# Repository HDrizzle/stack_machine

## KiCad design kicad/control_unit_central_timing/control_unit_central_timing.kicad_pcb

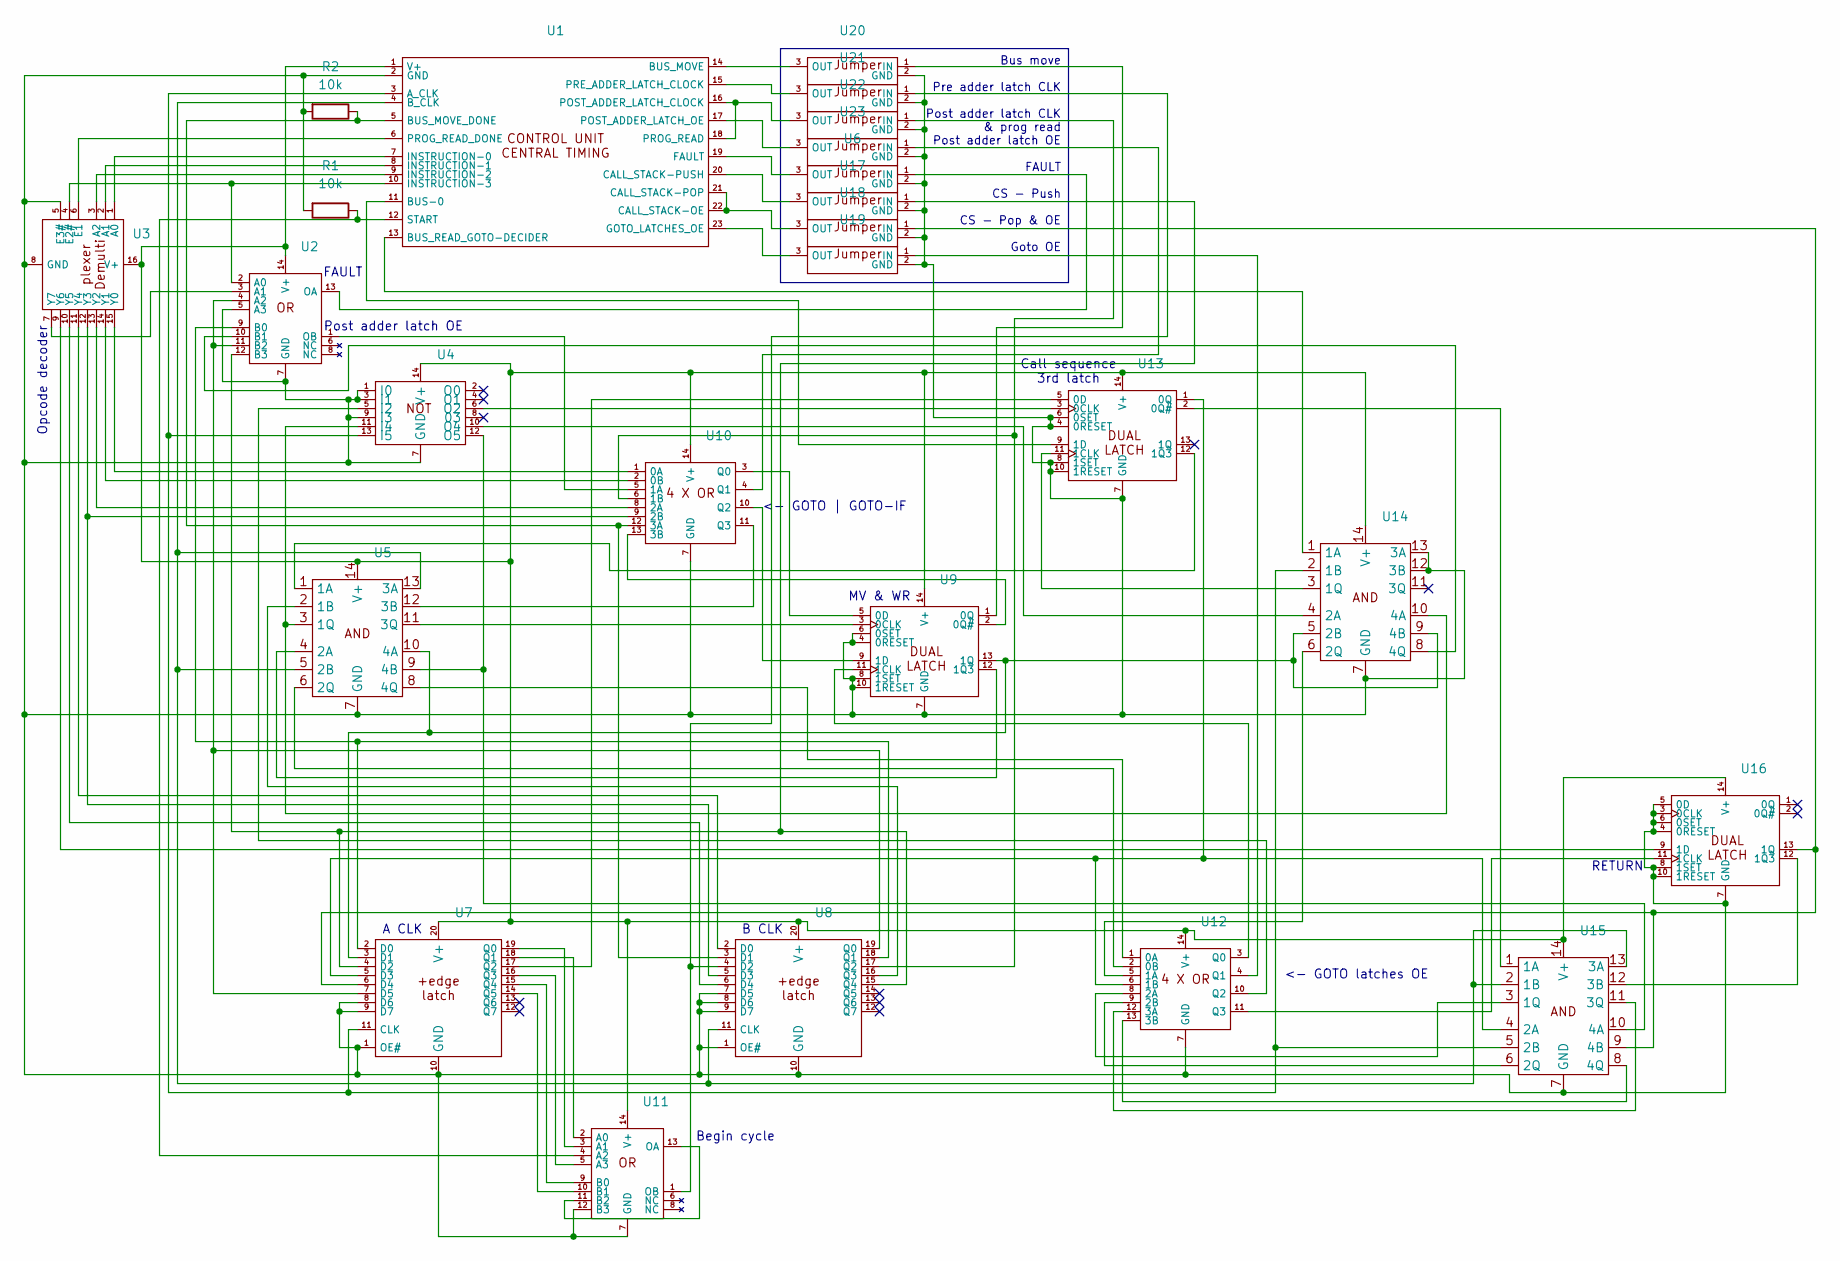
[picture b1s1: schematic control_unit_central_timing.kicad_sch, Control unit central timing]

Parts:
R1, R2: 10k; 0.4_pitch_resistor
U1: PinHeader_1x23_P2.54mm_Horizontal
U2, U4, U5, U9, U10, U11, U12, U13, U14, U15, U16: DIP-14_W7.62mm
U3: DIP-16_W7.62mm
U6, U17, U18, U19, U20, U21, U22, U23: jumper
U7, U8: DIP-20_W7.62mm

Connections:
unnamed: U1.3 (A_CLK), U4.13 (I5), U7.11 (CLK), U14.2 (1B), U15.5 (2B)
unnamed: U1.11 (BUS-0), U13.9 (1D)
unnamed: U1.14 (BUS_MOVE), U20.3 (OUT)
unnamed: R2.1, U1.5 (BUS_MOVE_DONE), U8.3 (D1), U10.12 (3A)
unnamed: U1.13 (BUS_READ_GOTO-DECIDER), U14.1 (1A)
unnamed: U1.4 (B_CLK), U5.5 (2B), U5.13 (3A), U8.11 (CLK), U15.2 (1B), U15.13 (3A)
unnamed: U1.21 (CALL_STACK-POP), U1.22 (CALL_STACK-OE), U18.3 (OUT)
unnamed: U1.20 (CALL_STACK-PUSH), U17.3 (OUT)
unnamed: U1.19 (FAULT), U6.3 (OUT)
unnamed: R1.2, R2.2, U1.2 (GND), U2.5 (A3), U2.7 (GND), U3.5 (E3#), U3.8 (GND), U4.1 (I0), U4.3 (I1), U4.7 (GND), U4.9 (I3), U5.7 (GND), U6.2 (GND), U7.1 (OE#), U7.8 (D6), U7.9 (D7), U7.10 (GND), U8.1 (OE#), U8.7 (D5), U8.8 (D6), U8.9 (D7), U8.10 (GND), U9.4 (0RESET), U9.6 (0SET), U9.7 (GND), U9.8 (1SET), U9.10 (1RESET), U10.7 (GND), U11.7 (GND), U11.12 (B3), U12.7 (GND), U13.4 (0RESET), U13.6 (0SET), U13.7 (GND), U13.8 (1SET), U13.10 (1RESET), U14.7 (GND), U14.12 (3B), U14.13 (3A), U15.7 (GND), U16.3 (0CLK), U16.4 (0RESET), U16.5 (0D), U16.6 (0SET), U16.7 (GND), U16.8 (1SET), U16.10 (1RESET), U17.2 (GND), U18.2 (GND), U19.2 (GND), U20.2 (GND), U21.2 (GND), U22.2 (GND), U23.2 (GND)
unnamed: U1.23 (GOTO_LATCHES_OE), U19.3 (OUT)
unnamed: U1.7 (INSTRUCTION-0), U3.1 (A0)
unnamed: U1.8 (INSTRUCTION-1), U3.2 (A1)
unnamed: U1.9 (INSTRUCTION-2), U3.3 (A2)
unnamed: U1.10 (INSTRUCTION-3), U2.2 (A0), U3.4 (E2#)
unnamed: U1.16 (POST_ADDER_LATCH_CLOCK), U1.18 (PROG_READ), U22.3 (OUT)
unnamed: U1.17 (POST_ADDER_LATCH_OE), U23.3 (OUT)
unnamed: U1.15 (PRE_ADDER_LATCH_CLOCK), U21.3 (OUT)
unnamed: U1.6 (PROG_READ_DONE), U3.6 (E1)
unnamed: R1.1, U1.12 (START), U11.4 (A2)
unnamed: U1.1 (V+), U2.14 (V+), U3.16 (V+), U4.14 (V+), U5.14 (V+), U7.20 (V+), U8.20 (V+), U9.14 (V+), U10.14 (V+), U11.14 (V+), U12.14 (V+), U13.14 (V+), U14.14 (V+), U15.14 (V+), U16.14 (V+)
unnamed: U2.3 (A1), U3.7 (Y7)
unnamed: U2.4 (A2), U2.11 (B2), U7.7 (D5), U8.19 (Q0)
unnamed: U2.9 (B0), U7.2 (D0), U8.18 (Q1)
unnamed: U2.13 (OA), U6.1 (IN)
unnamed: U3.11 (Y4), U8.2 (D0)
unnamed: U3.10 (Y5), U8.6 (D4)
unnamed: U5.2 (1B), U8.16 (Q3)
unnamed: U5.4 (2A), U9.12 (1Q3)
unnamed: U5.11 (3Q), U9.3 (0CLK)
unnamed: U3.15 (Y0), U10.1 (0A)
unnamed: U3.14 (Y1), U10.2 (0B)
unnamed: U2.1 (OB), U10.5 (1A)
unnamed: U8.17 (Q2), U10.6 (1B), U22.1 (IN)
unnamed: U3.13 (Y2), U10.8 (2A)
unnamed: U3.12 (Y3), U8.5 (D3), U10.9 (2B)
unnamed: U9.2 (0Q#), U10.13 (3B)
unnamed: U9.5 (0D), U10.3 (Q0)
unnamed: U10.4 (Q1), U23.1 (IN)
unnamed: U9.9 (1D), U10.10 (Q2)
unnamed: U5.12 (3B), U10.11 (Q3)
unnamed: U7.18 (Q1), U11.2 (A0)
unnamed: U7.19 (Q0), U11.3 (A1)
unnamed: U7.16 (Q3), U11.5 (A3)
unnamed: U7.15 (Q4), U11.9 (B0)
unnamed: U7.14 (Q5), U11.10 (B1)
unnamed: U11.11 (B2), U11.13 (OA)
unnamed: U8.4 (D2), U11.1 (OB), U21.1 (IN)
unnamed: U5.8 (4Q), U12.1 (0A)
unnamed: U5.6 (2Q), U12.2 (0B)
unnamed: U12.5 (1A), U14.6 (2Q)
unnamed: U7.5 (D3), U12.6 (1B), U13.1 (0Q), U15.4 (2A)
unnamed: U12.8 (2A), U15.3 (1Q)
unnamed: U12.9 (2B), U15.6 (2Q)
unnamed: U12.12 (3A), U15.11 (3Q)
unnamed: U12.13 (3B), U15.8 (4Q)
unnamed: U9.11 (1CLK), U12.3 (Q0)
unnamed: U12.4 (Q1), U19.1 (IN)
unnamed: U4.5 (I2), U12.10 (Q2)
unnamed: U12.11 (Q3), U16.11 (1CLK)
unnamed: U4.6 (O2), U13.3 (0CLK)
unnamed: U7.17 (Q2), U13.5 (0D)
unnamed: U13.2 (0Q#), U15.1 (1A)
unnamed: U13.11 (1CLK), U14.3 (1Q)
unnamed: U5.1 (1A), U13.12 (1Q3)
unnamed: U4.10 (O4), U14.4 (2A)
unnamed: U5.10 (4A), U7.3 (D1), U9.13 (1Q), U14.5 (2B), U14.9 (4B)
unnamed: U4.11 (I4), U5.3 (1Q), U14.10 (4A)
unnamed: U2.10 (B1), U14.8 (4Q)
unnamed: U15.12 (3B), U16.12 (1Q3)
unnamed: U4.12 (O5), U5.9 (4B), U15.10 (4A)
unnamed: U7.6 (D4), U15.9 (4B), U16.13 (1Q), U18.1 (IN)
unnamed: U3.9 (Y6), U16.9 (1D)
unnamed: U2.12 (B3), U7.4 (D2), U8.15 (Q4), U17.1 (IN)
unnamed: U9.1 (0Q), U20.1 (IN)

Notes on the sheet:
Bus move Pre adder latch CLK Post adder latch CLK & prog read Post adder latch OE FAULT CS - Push CS - Pop & OE Goto OE
Call sequence 3rd latch
Opcode decoder
MV & WR
<- GOTO latches OE
<- GOTO | GOTO-IF
A CLK
RETURN
B CLK
FAULT
Begin cycle
Post adder latch OE

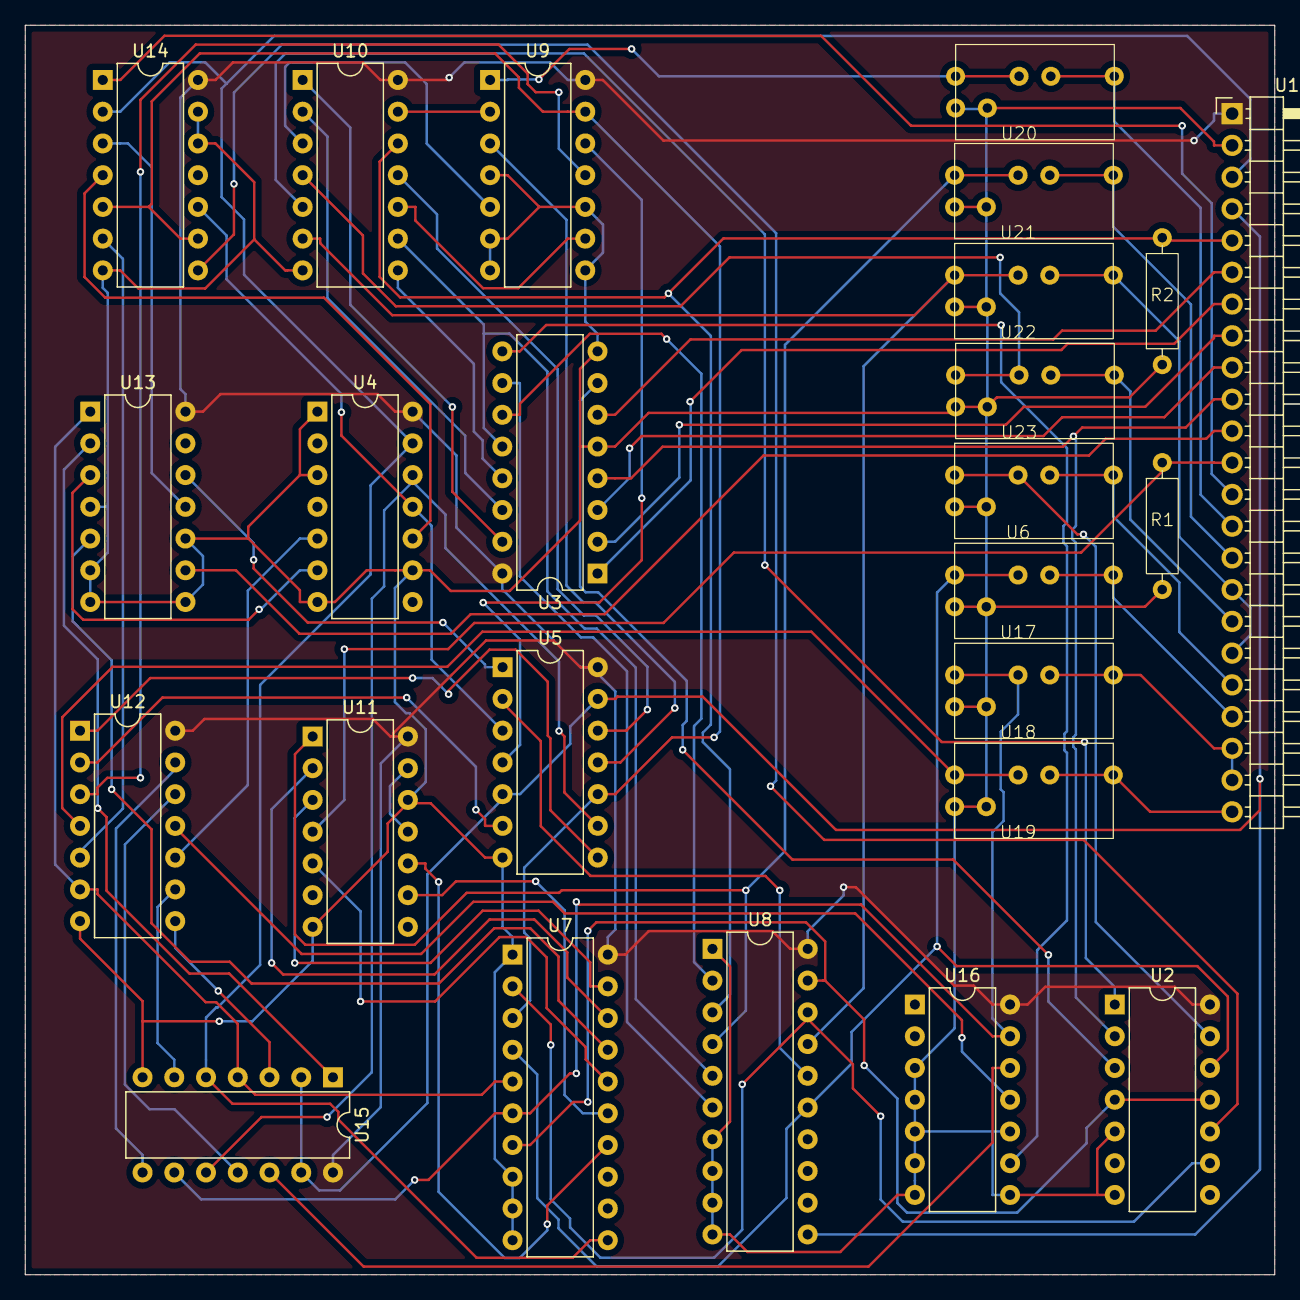
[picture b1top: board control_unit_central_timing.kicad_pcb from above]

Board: 2 copper layers, 100.0 x 100.0 mm, 25 parts (0 on the bottom side), 75 nets.

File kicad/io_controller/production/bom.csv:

Designator,Footprint,Quantity,Value,LCSC Part #
"R1, R2, R3, R4, R5",0.4_pitch_resistor,5,10k,
U1,PinHeader_1x23_P2.54mm_Vertical,1,~,
"U10, U11, U12, U13, U16, U9",DIP-14_W7.62mm,6,~,
"U14, U15",jumper,2,~,
"U2, U3, U5, U6",DIP-20_W7.62mm,4,~,
"U4, U7",PinHeader_1x16_P2.54mm_Vertical,2,~,

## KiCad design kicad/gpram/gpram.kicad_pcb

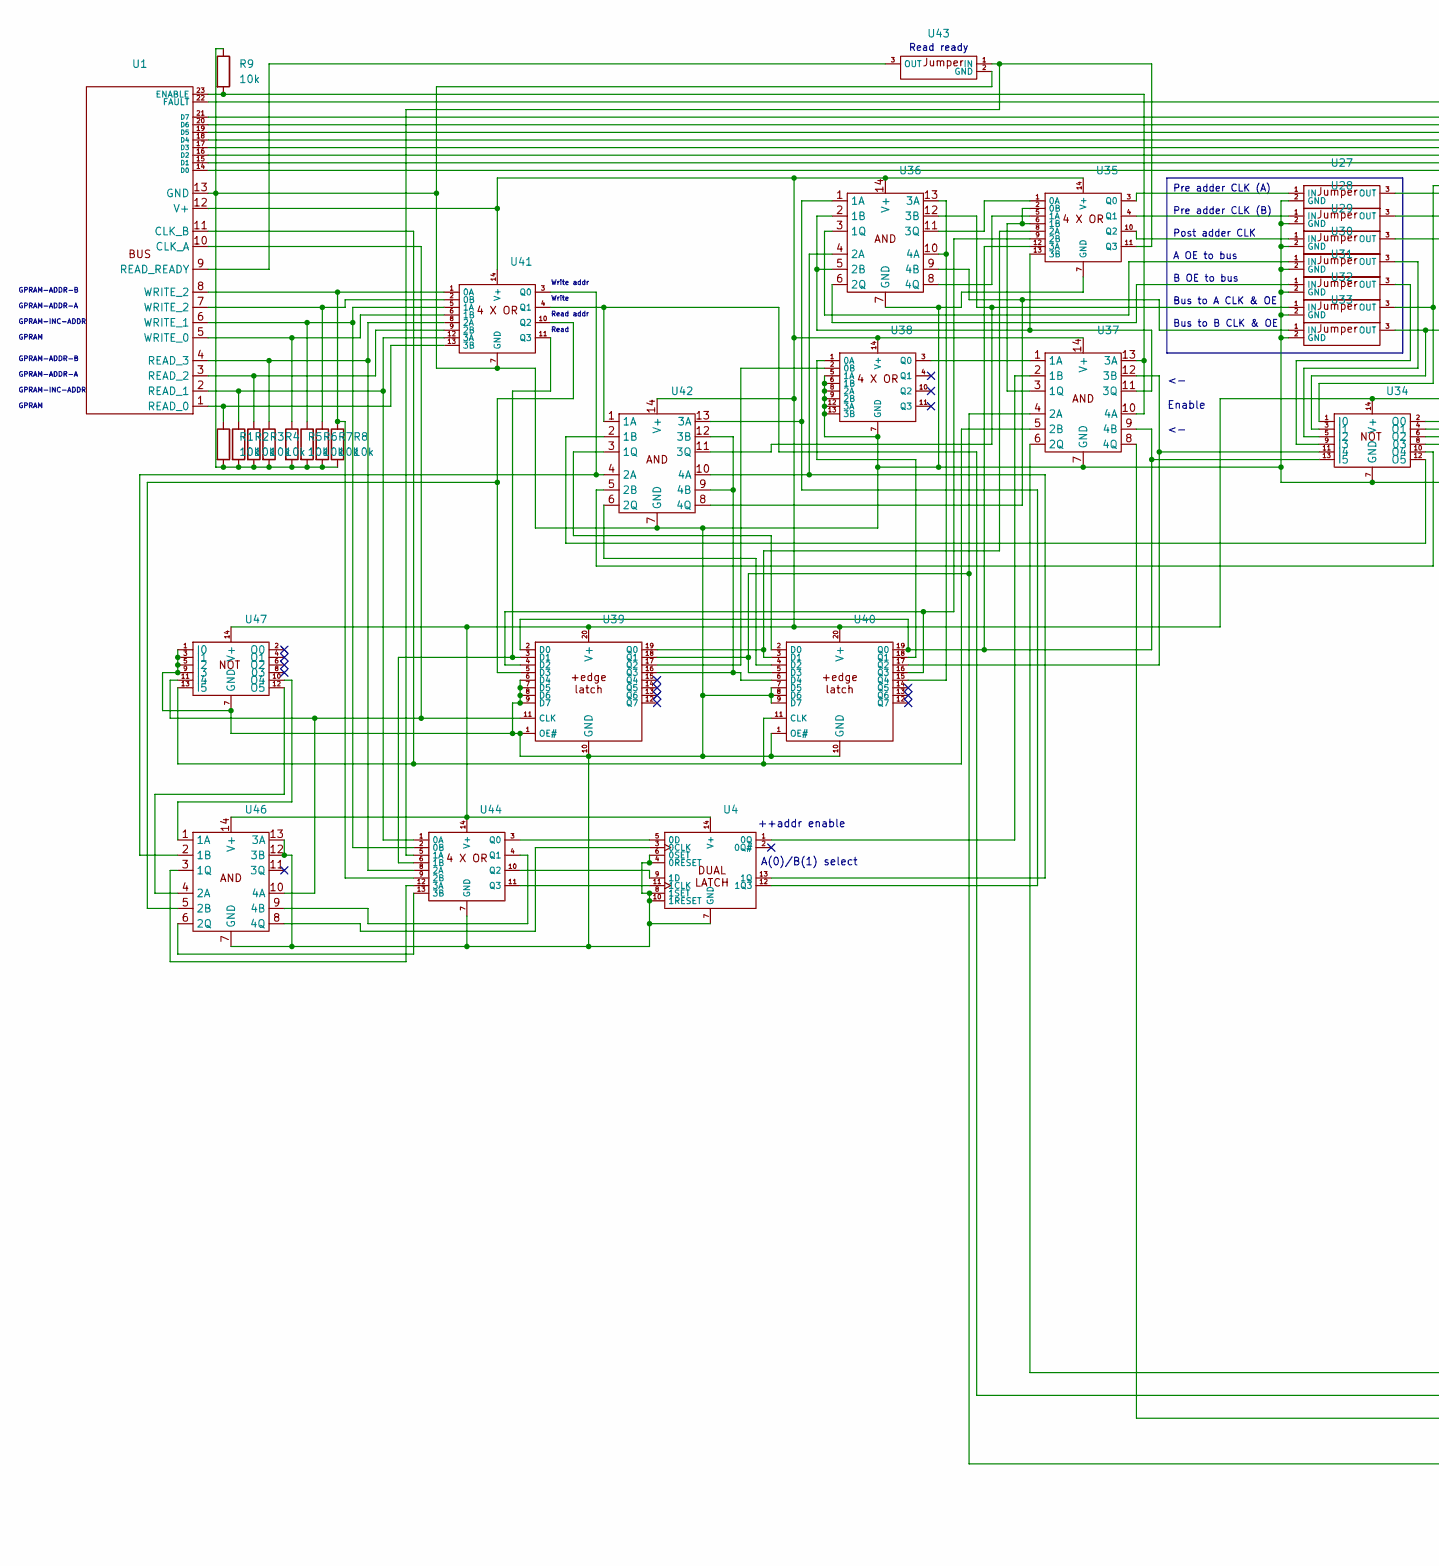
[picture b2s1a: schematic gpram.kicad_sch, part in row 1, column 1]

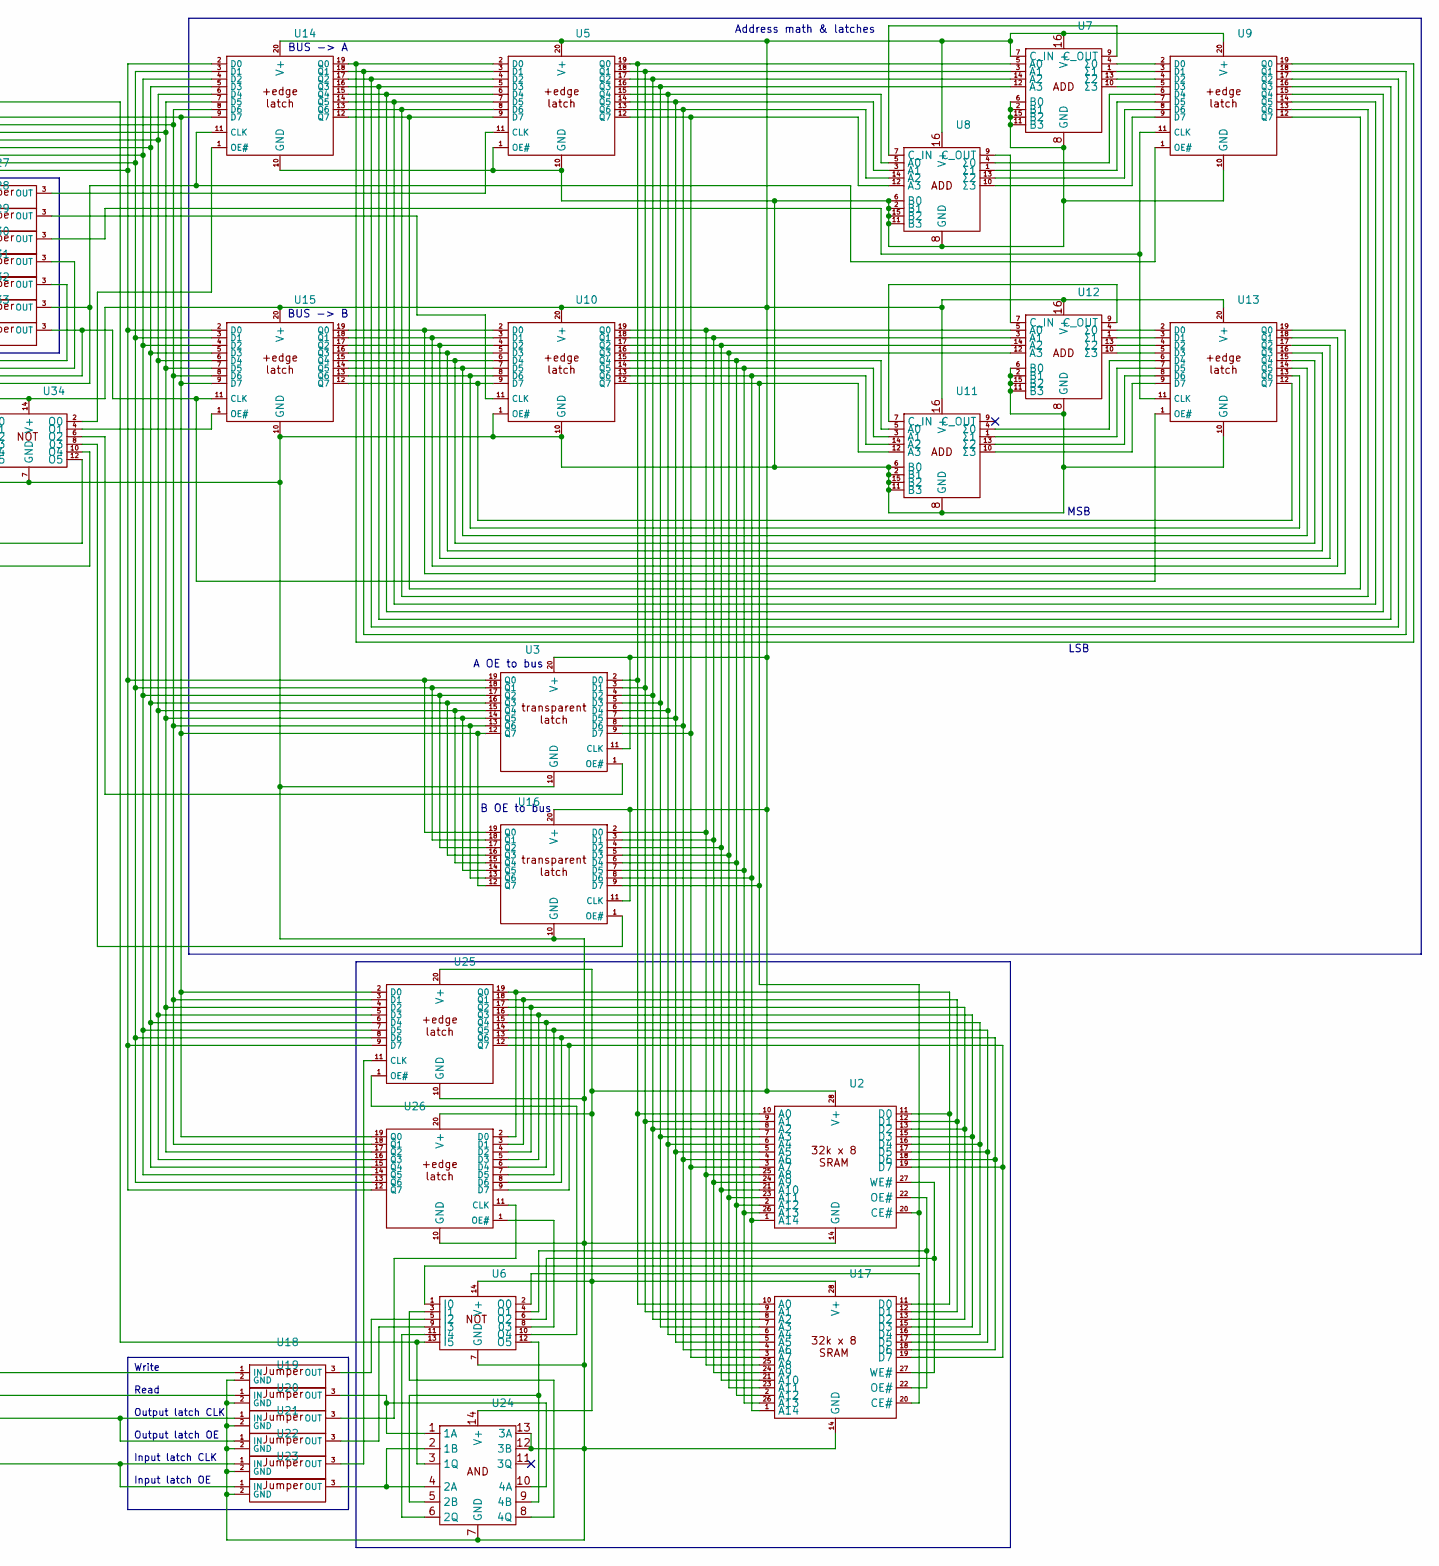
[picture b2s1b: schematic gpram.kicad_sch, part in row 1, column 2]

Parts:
R1, R2, R3, R4, R5, R6, R7, R8, R9: 10k; 0.4_pitch_resistor
U1: PinHeader_1x23_P2.54mm_Vertical
U2, U17: DIP-28_W15.24mm
U3, U5, U9, U10, U13, U14, U15, U16, U25, U26, U39, U40: DIP-20_W7.62mm
U4, U6, U24, U34, U35, U36, U37, U38, U41, U42, U44, U46, U47: DIP-14_W7.62mm
U7, U8, U11, U12: DIP-16_W7.62mm
U18, U19, U20, U21, U22, U23, U27, U28, U29, U30, U31, U32, U33, U43: jumper

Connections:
unnamed: U1.10 (CLK_A), U39.11 (CLK), U46.10 (4A), U47.11 (I4)
unnamed: U1.11 (CLK_B), U37.5 (2B), U40.11 (CLK), U47.13 (I5)
unnamed: U1.14 (D0), U3.19 (Q0), U14.2 (D0), U15.2 (D0), U16.19 (Q0), U25.9 (D7), U26.12 (Q7)
unnamed: U1.15 (D1), U3.18 (Q1), U14.3 (D1), U15.3 (D1), U16.18 (Q1), U25.8 (D6), U26.13 (Q6)
unnamed: U1.16 (D2), U3.17 (Q2), U14.4 (D2), U15.4 (D2), U16.17 (Q2), U25.7 (D5), U26.14 (Q5)
unnamed: U1.17 (D3), U3.16 (Q3), U14.5 (D3), U15.5 (D3), U16.16 (Q3), U25.6 (D4), U26.15 (Q4)
unnamed: U1.18 (D4), U3.15 (Q4), U14.6 (D4), U15.6 (D4), U16.15 (Q4), U25.5 (D3), U26.16 (Q3)
unnamed: U1.19 (D5), U3.14 (Q5), U14.7 (D5), U15.7 (D5), U16.14 (Q5), U25.4 (D2), U26.17 (Q2)
unnamed: U1.20 (D6), U3.13 (Q6), U14.8 (D6), U15.8 (D6), U16.13 (Q6), U25.3 (D1), U26.18 (Q1)
unnamed: U1.21 (D7), U3.12 (Q7), U14.9 (D7), U15.9 (D7), U16.12 (Q7), U25.2 (D0), U26.19 (Q0)
unnamed: R9.2, U1.23 (ENABLE), U37.10 (4A), U37.13 (3A)
unnamed: U1.22 (FAULT), U6.13 (I5), U24.3 (1Q)
unnamed: R1.2, R2.2, R3.2, R4.2, R5.2, R6.2, R7.2, R8.2, R9.1, U1.13 (GND), U2.14 (GND), U3.10 (GND), U4.4 (0RESET), U4.6 (0SET), U4.7 (GND), U4.8 (1SET), U4.10 (1RESET), U5.1 (OE#), U5.10 (GND), U6.7 (GND), U7.2 (B1), U7.6 (B0), U7.8 (GND), U7.11 (B3), U7.15 (B2), U8.2 (B1), U8.6 (B0), U8.8 (GND), U8.11 (B3), U8.15 (B2), U9.10 (GND), U10.1 (OE#), U10.10 (GND), U11.2 (B1), U11.6 (B0), U11.8 (GND), U11.11 (B3), U11.15 (B2), U12.2 (B1), U12.6 (B0), U12.8 (GND), U12.11 (B3), U12.15 (B2), U13.10 (GND), U14.10 (GND), U15.10 (GND), U16.10 (GND), U17.14 (GND), U18.2 (GND), U19.2 (GND), U20.2 (GND), U21.2 (GND), U22.2 (GND), U23.2 (GND), U24.7 (GND), U24.12 (3B), U24.13 (3A), U25.10 (GND), U26.10 (GND), U27.2 (GND), U28.2 (GND), U29.2 (GND), U30.2 (GND), U31.2 (GND), U32.2 (GND), U33.2 (GND), U34.7 (GND), U35.7 (GND), U36.7 (GND), U37.7 (GND), U38.5 (1A), U38.6 (1B), U38.7 (GND), U38.8 (2A), U38.9 (2B), U38.12 (3A), U38.13 (3B), U39.1 (OE#), U39.6 (D4), U39.7 (D5), U39.8 (D6), U39.9 (D7), U39.10 (GND), U40.1 (OE#), U40.7 (D5), U40.8 (D6), U40.9 (D7), U40.10 (GND), U41.7 (GND), U42.7 (GND), U43.2 (GND), U44.7 (GND), U46.7 (GND), U46.12 (3B), U46.13 (3A), U47.1 (I0), U47.3 (I1), U47.5 (I2), U47.7 (GND), U47.9 (I3)
unnamed: R1.1, U1.1 (READ_0), U41.13 (3B)
unnamed: R2.1, U1.2 (READ_1), U41.12 (3A), U44.1 (0A)
unnamed: R3.1, U1.3 (READ_2), U41.9 (2B)
unnamed: R4.1, U1.4 (READ_3), U41.8 (2A), U44.8 (2A)
unnamed: U1.9 (READ_READY), U43.3 (OUT)
unnamed: U1.12 (V+), U2.28 (V+), U3.11 (CLK), U3.20 (V+), U4.14 (V+), U5.20 (V+), U6.14 (V+), U7.7 (C_IN), U7.16 (V+), U8.16 (V+), U9.20 (V+), U10.20 (V+), U11.16 (V+), U12.16 (V+), U13.20 (V+), U14.20 (V+), U15.20 (V+), U16.11 (CLK), U16.20 (V+), U17.28 (V+), U24.14 (V+), U25.20 (V+), U26.20 (V+), U34.14 (V+), U35.14 (V+), U36.14 (V+), U37.14 (V+), U38.14 (V+), U39.20 (V+), U40.20 (V+), U41.14 (V+), U42.14 (V+), U44.14 (V+), U46.14 (V+), U47.14 (V+)
unnamed: R5.1, U1.5 (WRITE_0), U41.6 (1B)
unnamed: R6.1, U1.6 (WRITE_1), U41.5 (1A), U44.2 (0B)
unnamed: U3.1 (OE#), U34.6 (O2)
unnamed: U4.3 (0CLK), U46.8 (4Q)
unnamed: U4.5 (0D), U44.3 (Q0)
unnamed: U4.11 (1CLK), U44.11 (Q3)
unnamed: U4.9 (1D), U44.10 (Q2)
unnamed: U7.9 (C_OUT), U8.7 (C_IN)
unnamed: U7.4 (Σ0), U9.2 (D0)
unnamed: U7.1 (Σ1), U9.3 (D1)
unnamed: U7.13 (Σ2), U9.4 (D2)
unnamed: U7.10 (Σ3), U9.5 (D3)
unnamed: U8.4 (Σ0), U9.6 (D4)
unnamed: U8.1 (Σ1), U9.7 (D5)
unnamed: U8.13 (Σ2), U9.8 (D6)
unnamed: U8.10 (Σ3), U9.9 (D7)
unnamed: U10.11 (CLK), U28.3 (OUT)
unnamed: U10.2 (D0), U13.19 (Q0), U15.19 (Q0)
unnamed: U10.3 (D1), U13.18 (Q1), U15.18 (Q1)
unnamed: U10.4 (D2), U13.17 (Q2), U15.17 (Q2)
unnamed: U10.5 (D3), U13.16 (Q3), U15.16 (Q3)
unnamed: U10.6 (D4), U13.15 (Q4), U15.15 (Q4)
unnamed: U10.7 (D5), U13.14 (Q5), U15.14 (Q5)
unnamed: U10.8 (D6), U13.13 (Q6), U15.13 (Q6)
unnamed: U10.9 (D7), U13.12 (Q7), U15.12 (Q7)
unnamed: U2.25 (A8), U10.19 (Q0), U12.5 (A0), U16.2 (D0), U17.25 (A8)
unnamed: U2.24 (A9), U10.18 (Q1), U12.3 (A1), U16.3 (D1), U17.24 (A9)
unnamed: U2.21 (A10), U10.17 (Q2), U12.14 (A2), U16.4 (D2), U17.21 (A10)
unnamed: U2.23 (A11), U10.16 (Q3), U12.12 (A3), U16.5 (D3), U17.23 (A11)
unnamed: U2.2 (A12), U10.15 (Q4), U11.5 (A0), U16.6 (D4), U17.2 (A12)
unnamed: U2.26 (A13), U10.14 (Q5), U11.3 (A1), U16.7 (D5), U17.26 (A13)
unnamed: U2.1 (A14), U10.13 (Q6), U11.14 (A2), U16.8 (D6), U17.1 (A14)
unnamed: U2.20 (CE#), U6.1 (I0), U10.12 (Q7), U11.12 (A3), U16.9 (D7)
unnamed: U11.7 (C_IN), U12.9 (C_OUT)
unnamed: U11.4 (Σ0), U13.6 (D4)
unnamed: U11.1 (Σ1), U13.7 (D5)
unnamed: U11.13 (Σ2), U13.8 (D6)
unnamed: U11.10 (Σ3), U13.9 (D7)
unnamed: U8.9 (C_OUT), U12.7 (C_IN)
unnamed: U12.4 (Σ0), U13.2 (D0)
unnamed: U12.1 (Σ1), U13.3 (D1)
unnamed: U12.13 (Σ2), U13.4 (D2)
unnamed: U12.10 (Σ3), U13.5 (D3)
unnamed: U9.11 (CLK), U13.11 (CLK), U29.3 (OUT)
unnamed: U13.1 (OE#), U15.11 (CLK), U33.3 (OUT), U34.3 (I1)
unnamed: U9.1 (OE#), U14.11 (CLK), U32.3 (OUT), U34.1 (I0)
unnamed: U14.1 (OE#), U34.2 (O0)
unnamed: U5.2 (D0), U9.19 (Q0), U14.19 (Q0)
unnamed: U5.3 (D1), U9.18 (Q1), U14.18 (Q1)
unnamed: U5.4 (D2), U9.17 (Q2), U14.17 (Q2)
unnamed: U5.5 (D3), U9.16 (Q3), U14.16 (Q3)
unnamed: U5.6 (D4), U9.15 (Q4), U14.15 (Q4)
unnamed: U5.7 (D5), U9.14 (Q5), U14.14 (Q5)
unnamed: U5.8 (D6), U9.13 (Q6), U14.13 (Q6)
unnamed: U5.9 (D7), U9.12 (Q7), U14.12 (Q7)
unnamed: U15.1 (OE#), U34.4 (O1)
unnamed: U16.1 (OE#), U34.8 (03)
unnamed: U2.10 (A0), U3.2 (D0), U5.19 (Q0), U7.5 (A0), U17.10 (A0)
unnamed: U2.9 (A1), U3.3 (D1), U5.18 (Q1), U7.3 (A1), U17.9 (A1)
unnamed: U2.8 (A2), U3.4 (D2), U5.17 (Q2), U7.14 (A2), U17.8 (A2)
unnamed: U2.7 (A3), U3.5 (D3), U5.16 (Q3), U7.12 (A3), U17.7 (A3)
unnamed: U2.6 (A4), U3.6 (D4), U5.15 (Q4), U8.5 (A0), U17.6 (A4)
unnamed: U2.5 (A5), U3.7 (D5), U5.14 (Q5), U8.3 (A1), U17.5 (A5)
unnamed: U2.4 (A6), U3.8 (D6), U5.13 (Q6), U8.14 (A2), U17.4 (A6)
unnamed: U2.3 (A7), U3.9 (D7), U5.12 (Q7), U8.12 (A3), U17.3 (A7)
unnamed: U6.2 (O0), U17.20 (CE#)
unnamed: U2.11 (D0), U17.11 (D0), U25.19 (Q0), U26.2 (D0)
unnamed: U2.12 (D1), U17.12 (D1), U25.18 (Q1), U26.3 (D1)
unnamed: U2.13 (D2), U17.13 (D2), U25.17 (Q2), U26.4 (D2)
unnamed: U2.15 (D3), U17.15 (D3), U25.16 (Q3), U26.5 (D3)
unnamed: U2.16 (D4), U17.16 (D4), U25.15 (Q4), U26.6 (D4)
unnamed: U2.17 (D5), U17.17 (D5), U25.14 (Q5), U26.7 (D5)
unnamed: U2.18 (D6), U17.18 (D6), U25.13 (Q6), U26.8 (D6)
unnamed: U2.19 (D7), U17.19 (D7), U25.12 (Q7), U26.9 (D7)
unnamed: U2.22 (OE#), U6.4 (O1), U17.22 (OE#)
unnamed: U2.27 (WE#), U6.6 (O2), U17.27 (WE#)
unnamed: U18.1 (IN), U37.6 (2Q)
unnamed: U6.5 (I2), U18.3 (OUT)
unnamed: U19.1 (IN), U41.4 (Q1), U42.1 (1A)
unnamed: U19.3 (OUT), U24.1 (1A), U24.10 (4A)
unnamed: U20.1 (IN), U21.1 (IN), U37.8 (4Q)
unnamed: U20.3 (OUT), U26.11 (CLK)
unnamed: U6.9 (I3), U21.3 (OUT)
unnamed: U22.1 (IN), U23.1 (IN), U37.4 (2A), U39.18 (Q1), U40.5 (D3)
unnamed: U22.3 (OUT), U25.11 (CLK)
unnamed: U23.3 (OUT), U24.2 (1B), U24.4 (2A)
unnamed: U6.12 (O5), U24.5 (2B), U24.9 (4B)
unnamed: U6.11 (I4), U24.6 (2Q)
unnamed: U6.3 (I1), U24.8 (4Q)
unnamed: U6.10 (O4), U25.1 (OE#)
unnamed: U6.8 (03), U26.1 (OE#)
unnamed: U27.1 (IN), U35.3 (Q0)
unnamed: U5.11 (CLK), U27.3 (OUT)
unnamed: U28.1 (IN), U35.4 (Q1)
unnamed: U29.1 (IN), U35.10 (Q2)
unnamed: U30.1 (IN), U36.3 (1Q)
unnamed: U30.3 (OUT), U34.5 (I2)
unnamed: U31.1 (IN), U36.6 (2Q)
unnamed: U31.3 (OUT), U34.9 (I3)
unnamed: U32.1 (IN), U36.12 (3B), U42.11 (3Q)
unnamed: U33.1 (IN), U36.9 (4B), U42.8 (4Q)
unnamed: U34.11 (I4), U37.12 (3B), U40.17 (Q2)
unnamed: U34.13 (I5), U35.12 (3A), U37.9 (4B), U39.2 (D0), U40.19 (Q0)
unnamed: U34.10 (O4), U42.5 (2B)
unnamed: U34.12 (O5), U42.2 (1B)
unnamed: U35.1 (0A), U36.11 (3Q)
unnamed: U35.2 (0B), U35.6 (1B), U37.3 (1Q)
unnamed: U35.5 (1A), U36.8 (4Q)
unnamed: U35.8 (2A), U39.19 (Q0), U40.3 (D1)
unnamed: U35.9 (2B), U39.4 (D2), U40.16 (Q3)
unnamed: U35.13 (3B), U36.2 (1B), U36.5 (2B), U37.11 (3Q)
unnamed: U35.11 (Q3), U43.1 (IN), U44.5 (1A)
unnamed: U4.12 (1Q3), U36.1 (1A), U42.13 (3A)
unnamed: U4.13 (1Q), U36.4 (2A), U42.10 (4A)
unnamed: U36.10 (4A), U36.13 (3A), U40.15 (Q4)
unnamed: U37.1 (1A), U38.3 (Q0)
unnamed: U4.1 (0Q), U37.2 (1B)
unnamed: U38.1 (0A), U40.18 (Q1)
unnamed: U38.2 (0B), U39.17 (Q2)
unnamed: U39.3 (D1), U41.11 (Q3), U44.6 (1B)
unnamed: U39.5 (D3), U41.10 (Q2), U46.5 (2B)
unnamed: U39.16 (Q3), U40.6 (D4), U42.9 (4B), U42.12 (3B)
unnamed: U40.2 (D0), U42.3 (1Q)
unnamed: U40.4 (D2), U42.6 (2Q)
unnamed: R8.1, U1.8 (WRITE_2), U41.1 (0A), U44.9 (2B)
unnamed: R7.1, U1.7 (WRITE_2), U41.2 (0B)
unnamed: U41.3 (Q0), U42.4 (2A), U46.2 (1B)
unnamed: U44.12 (3A), U46.3 (1Q)
unnamed: U44.13 (3B), U46.6 (2Q)
unnamed: U44.4 (Q1), U46.9 (4B)
unnamed: U46.1 (1A), U47.10 (O4)
unnamed: U46.4 (2A), U47.12 (O5)

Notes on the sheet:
Pre adder CLK (A) Pre adder CLK (B) Post adder CLK A OE to bus B OE to bus Bus to A CLK & OE Bus to B CLK & OE
Write Read Output latch CLK Output latch OE Input latch CLK Input latch OE
Address math & latches
BUS -> B
Write addr Write Read addr Read
GPRAM-ADDR-B GPRAM-ADDR-A GPRAM-INC-ADDR GPRAM
A(0)/B(1) select
BUS -> A
LSB
<- Enable <-
B OE to bus
++addr enable
MSB
Read ready
A OE to bus

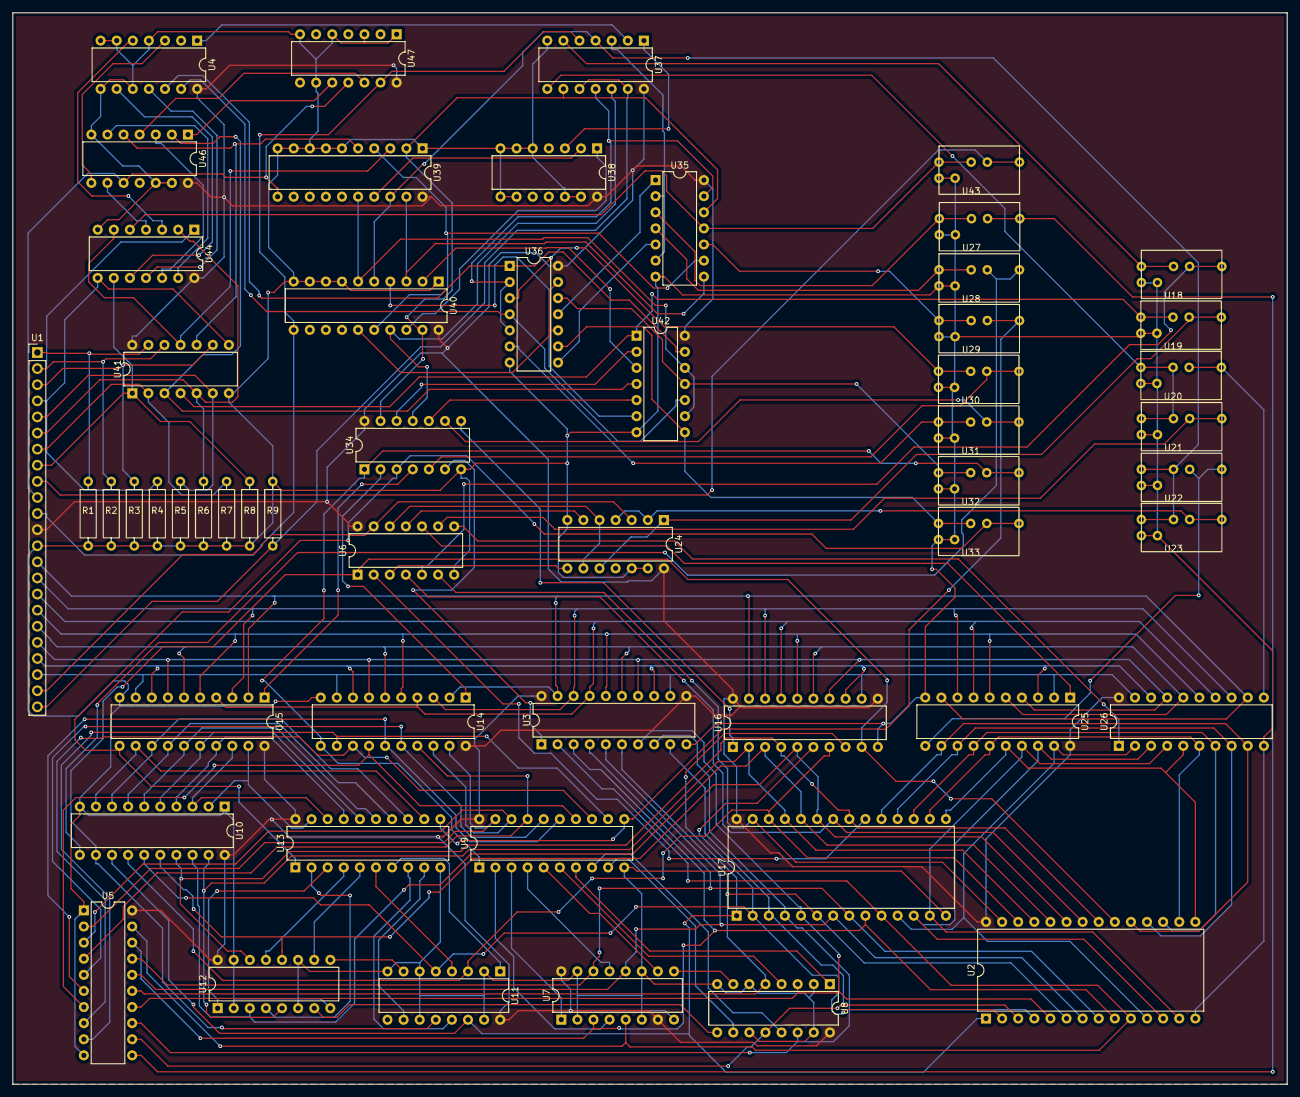
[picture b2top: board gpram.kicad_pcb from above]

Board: 2 copper layers, 201.0 x 169.0 mm, 55 parts (0 on the bottom side), 151 nets.

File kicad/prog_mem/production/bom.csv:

Designator,Footprint,Quantity,Value,LCSC Part #
D1,D_A-405_P7.62mm_Horizontal,1,D,
"R1, R10, R2, R3, R4, R5, R6, R7, R8, R9",0.4_pitch_resistor,10,10k,
"U1, U7",DIP-32_W15.24mm,2,~,
"U10, U11, U13, U14, U16, U21, U5, U8",DIP-20_W7.62mm,8,~,
"U12, U32, U33, U38, U4, U6, U9",DIP-14_W7.62mm,7,~,
"U15, U17, U18, U20, U22, U23, U24, U25",jumper,8,~,
U19,PinHeader_1x16_P2.54mm_Vertical,1,~,
U2,PinHeader_1x39_P2.54mm_Vertical,1,~,
U3,PinHeader_1x10_P2.54mm_Horizontal,1,~,

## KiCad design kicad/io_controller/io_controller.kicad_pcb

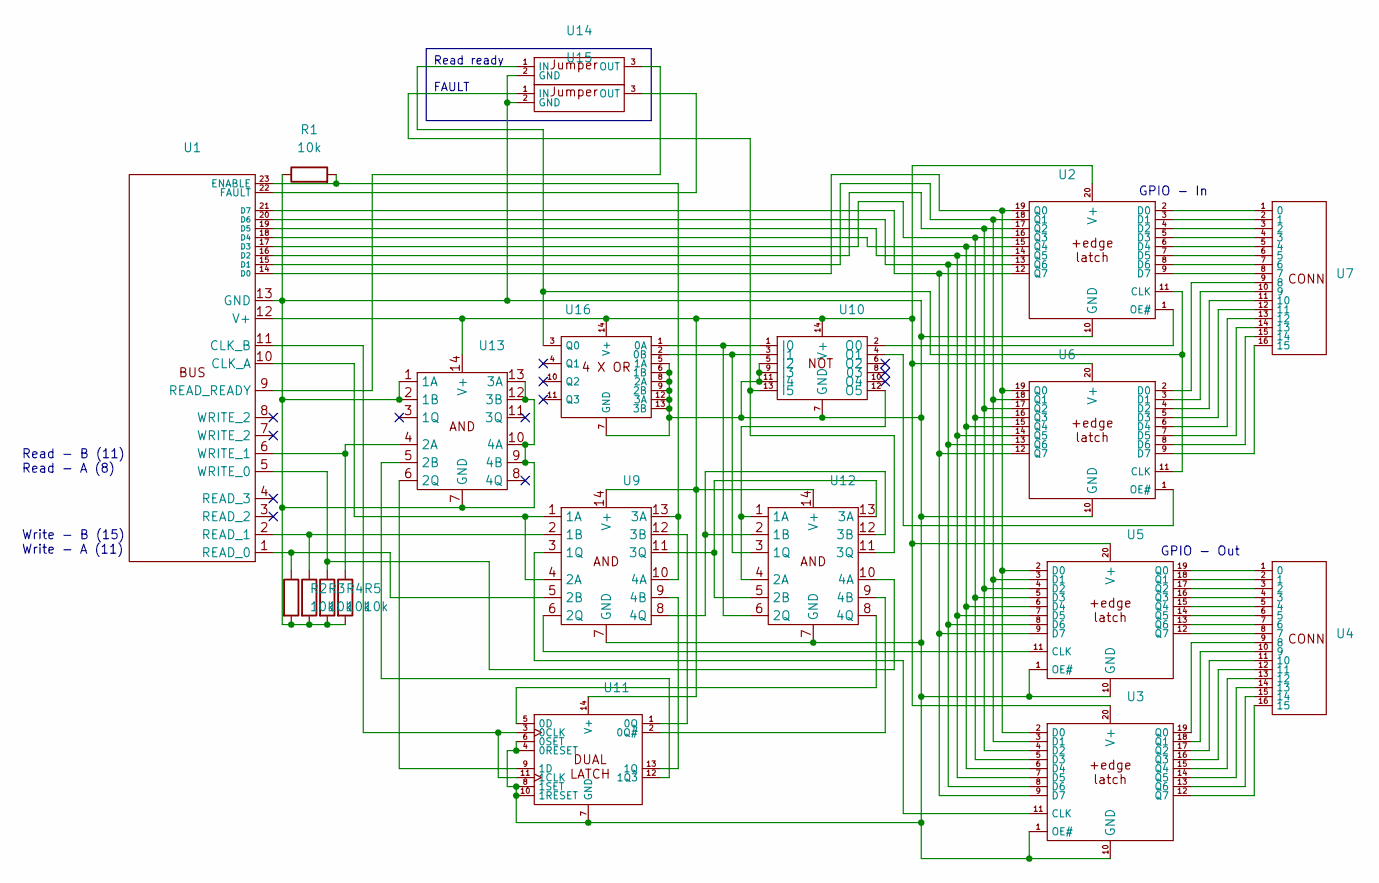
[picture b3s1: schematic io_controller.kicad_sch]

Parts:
R1, R2, R3, R4, R5: 10k; 0.4_pitch_resistor
U1: PinHeader_1x23_P2.54mm_Vertical
U2, U3, U5, U6: DIP-20_W7.62mm
U4, U7: PinHeader_1x16_P2.54mm_Vertical
U9, U10, U11, U12, U13, U16: DIP-14_W7.62mm
U14, U15: jumper

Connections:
unnamed: U1.10 (CLK_A), U9.1 (1A), U9.4 (2A)
unnamed: U1.11 (CLK_B), U11.3 (0CLK), U11.11 (1CLK)
unnamed: U1.14 (D0), U2.19 (Q0), U3.2 (D0), U5.2 (D0), U6.19 (Q0)
unnamed: U1.15 (D1), U2.18 (Q1), U3.3 (D1), U5.3 (D1), U6.18 (Q1)
unnamed: U1.16 (D2), U2.17 (Q2), U3.4 (D2), U5.4 (D2), U6.17 (Q2)
unnamed: U1.17 (D3), U2.16 (Q3), U3.5 (D3), U5.5 (D3), U6.16 (Q3)
unnamed: U1.18 (D4), U2.15 (Q4), U3.6 (D4), U5.6 (D4), U6.15 (Q4)
unnamed: U1.19 (D5), U2.14 (Q5), U3.7 (D5), U5.7 (D5), U6.14 (Q5)
unnamed: U1.20 (D6), U2.13 (Q6), U3.8 (D6), U5.8 (D6), U6.13 (Q6)
unnamed: U1.21 (D7), U2.12 (Q7), U3.9 (D7), U5.9 (D7), U6.12 (Q7)
unnamed: R1.2, U1.23 (ENABLE), U9.10 (4A), U9.13 (3A)
unnamed: U1.22 (FAULT), U15.3 (OUT)
unnamed: R1.1, R2.2, R3.2, R4.2, R5.2, U1.13 (GND), U2.10 (GND), U3.1 (OE#), U3.10 (GND), U5.1 (OE#), U5.10 (GND), U6.10 (GND), U9.7 (GND), U10.5 (I2), U10.7 (GND), U10.9 (I3), U10.11 (I4), U11.4 (0RESET), U11.6 (0SET), U11.7 (GND), U11.8 (1SET), U11.10 (1RESET), U12.7 (GND), U13.1 (1A), U13.2 (1B), U13.7 (GND), U13.9 (4B), U13.10 (4A), U13.12 (3B), U13.13 (3A), U14.2 (GND), U15.2 (GND), U16.5 (1A), U16.6 (1B), U16.7 (GND), U16.8 (2A), U16.9 (2B), U16.12 (3A), U16.13 (3B)
unnamed: R2.1, U1.1 (READ_0), U9.5 (2B)
unnamed: R3.1, U1.2 (READ_1), U9.2 (1B)
unnamed: U1.9 (READ_READY), U14.3 (OUT)
unnamed: U1.12 (V+), U2.20 (V+), U3.20 (V+), U5.20 (V+), U6.20 (V+), U9.14 (V+), U10.14 (V+), U11.14 (V+), U12.14 (V+), U13.14 (V+), U16.14 (V+)
unnamed: R4.1, U1.5 (WRITE_0), U12.10 (4A)
unnamed: R5.1, U1.6 (WRITE_1), U13.4 (2A)
unnamed: U2.2 (D0), U7.1 (0)
unnamed: U2.3 (D1), U7.2 (1)
unnamed: U2.4 (D2), U7.3 (2)
unnamed: U2.5 (D3), U7.4 (3)
unnamed: U2.6 (D4), U7.5 (4)
unnamed: U2.7 (D5), U7.6 (5)
unnamed: U2.8 (D6), U7.7 (6)
unnamed: U2.9 (D7), U7.8 (7)
unnamed: U3.11 (CLK), U9.3 (1Q)
unnamed: U3.19 (Q0), U4.9 (8)
unnamed: U3.18 (Q1), U4.10 (9)
unnamed: U3.17 (Q2), U4.11 (10)
unnamed: U3.16 (Q3), U4.12 (11)
unnamed: U3.15 (Q4), U4.13 (12)
unnamed: U3.14 (Q5), U4.14 (13)
unnamed: U3.13 (Q6), U4.15 (14)
unnamed: U3.12 (Q7), U4.16 (15)
unnamed: U4.1 (0), U5.19 (Q0)
unnamed: U4.2 (1), U5.18 (Q1)
unnamed: U4.3 (2), U5.17 (Q2)
unnamed: U4.4 (3), U5.16 (Q3)
unnamed: U4.5 (4), U5.15 (Q4)
unnamed: U4.6 (5), U5.14 (Q5)
unnamed: U4.7 (6), U5.13 (Q6)
unnamed: U4.8 (7), U5.12 (Q7)
unnamed: U5.11 (CLK), U9.6 (2Q)
unnamed: U6.2 (D0), U7.9 (8)
unnamed: U6.3 (D1), U7.10 (9)
unnamed: U6.4 (D2), U7.11 (10)
unnamed: U6.5 (D3), U7.12 (11)
unnamed: U6.6 (D4), U7.13 (12)
unnamed: U6.7 (D5), U7.14 (13)
unnamed: U6.8 (D6), U7.15 (14)
unnamed: U6.9 (D7), U7.16 (15)
unnamed: U10.1 (I0), U12.6 (2Q), U16.1 (0A)
unnamed: U10.3 (I1), U12.3 (1Q), U16.2 (0B)
unnamed: U10.13 (I5), U12.11 (3Q), U15.1 (IN)
unnamed: U2.1 (OE#), U10.2 (O0)
unnamed: U6.1 (OE#), U10.4 (O1)
unnamed: U10.12 (O5), U12.1 (1A), U12.4 (2A)
unnamed: U11.5 (0D), U12.8 (4Q)
unnamed: U11.2 (0Q#), U12.9 (4B)
unnamed: U9.12 (3B), U11.1 (0Q)
unnamed: U11.9 (1D), U13.6 (2Q)
unnamed: U11.12 (1Q3), U13.5 (2B)
unnamed: U9.9 (4B), U11.13 (1Q)
unnamed: U9.8 (4Q), U12.2 (1B), U12.12 (3B)
unnamed: U9.11 (3Q), U12.5 (2B), U12.13 (3A)
unnamed: U2.11 (CLK), U6.11 (CLK), U14.1 (IN), U16.3 (Q0)

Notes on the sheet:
Read ready FAULT
Read - B (11) Read - A (8)
GPIO - Out
GPIO - In
Write - B (15) Write - A (11)
